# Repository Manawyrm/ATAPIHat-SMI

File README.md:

ATAPIHat-SMI
=============================

### Overview

This is an experimental adapter PCB for the pata-gpio driver.  
The pinout was chosen deliberately to support faster SMI and BCM2835 register modes,  
which are not yet supported in the kernel driver. 

Rev.A testboards were ordered but not tested yet. **Proceed at your own risk.** 

### Manufacturing

Manufacturing files for JLCs automatic assembly service can be found at `gerbers/RevA/ATAPIHat-SMI/`.  
5 adapter boards cost ~15$ (incl. components). 

### Additional info 

[Schematic](gerbers/RevA/ATAPIHat-SMI/ATAPIHat-SMI.pdf)  
[Interactive BOM](https://tbspace.de/content/downloads/atapihat-smi-ibom-reva.html)  
[Bitbanged-GPIO Kernel driver](https://github.com/Manawyrm/pata-gpio)  

### Credits
The PCB layout was done by [@Toble_Miner](https://github.com/TobleMiner)! Thanks!

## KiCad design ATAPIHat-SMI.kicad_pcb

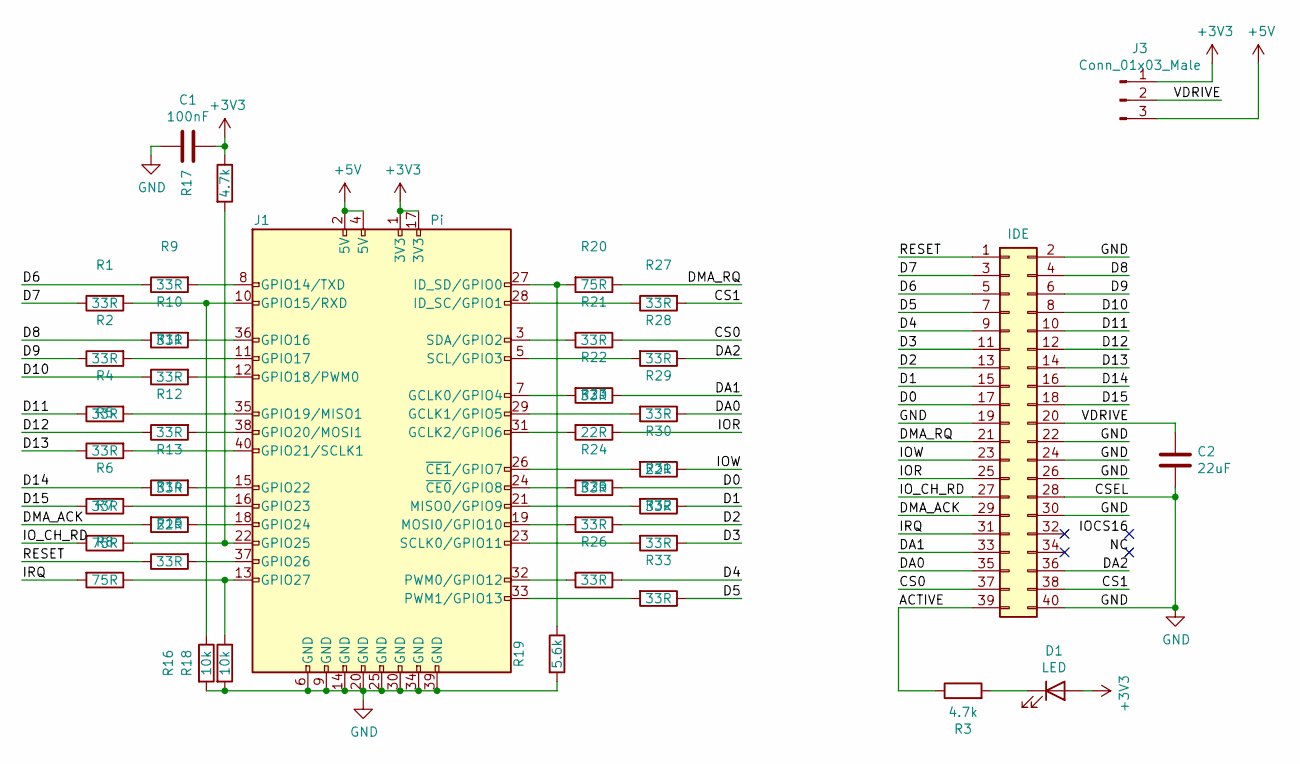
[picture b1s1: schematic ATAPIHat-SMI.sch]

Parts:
C1: 100nF; C_0402_1005Metric; LCSC C1525
C2: 22uF; C_0805_2012Metric; LCSC C45783
D1: LED; LED_0603_1608Metric; LCSC C72043
J1: Pi; PinSocket_2x20_P2.54mm_Vertical
J2: IDE; IDC-Header_2x20_P2.54mm_Vertical
J3: Conn_01x03_Male; SolderJumper-3_P1.3mm_Bridged12_Pad1.0x1.5mm
R1, R2, R4, R5, R6, R9, R10, R11, R12, R13, R15, R21, R22, R24, R25, R26, R27, R28, R29, R31, R32, R33: 33R; R_0402_1005Metric; LCSC C25105
R3, R17: 4.7k; R_0402_1005Metric; LCSC C25900
R7, R8, R20: 75R; R_0402_1005Metric; LCSC C25133
R14, R23, R30: 22R; R_0402_1005Metric; LCSC C25092
R16, R18: 10k; R_0402_1005Metric; LCSC C25744
R19: 5.6k; R_0402_1005Metric; LCSC C25908

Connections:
+3V3: C1.1, D1.2 (A), J1.1 (3V3), J1.17 (3V3), J3.1, R17.1
+5V: J1.2 (5V), J1.4 (5V), J3.3
/ACTIVE: J2.39, R3.1
/CS0: J2.37, R21.1
/CS1: J2.38, R27.2
/D0: J2.17, R24.1
/D1: J2.15, R31.1
/D2: J2.13, R25.1
/D3: J2.11, R32.1
/D4: J2.9, R26.1
/D5: J2.7, R33.1
/D6: J2.5, R9.1
/D7: J2.3, R1.1
/D8: J2.4, R10.1
/D9: J2.6, R2.1
/D10: J2.8, R11.1
/D11: J2.10, R4.1
/D12: J2.12, R12.1
/D13: J2.14, R5.1
/D14: J2.16, R13.1
/D15: J2.18, R6.1
/DA0: J2.35, R29.1
/DA1: J2.33, R22.1
/DA2: J2.36, R28.1
/DMA_ACK: J2.29, R14.2
/DMA_RQ: J2.21, R20.1
/IOR: J2.25, R23.1
/IOW: J2.23, R30.1
/IO_CH_RD: J2.27, R7.2
/IRQ: J2.31, R8.2
/RESET: J2.1, R15.1
/VDRIVE: C2.1, J2.20, J3.2
GND: C1.2, C2.2, J1.6 (GND), J1.9 (GND), J1.14 (GND), J1.20 (GND), J1.25 (GND), J1.30 (GND), J1.34 (GND), J1.39 (GND), J2.2, J2.19, J2.22, J2.24, J2.26, J2.28, J2.30, J2.40, R16.2, R18.2, R19.2
unnamed: D1.1 (K), R3.2
unnamed: J1.3 (SDA/GPIO2), R21.2
unnamed: J1.5 (SCL/GPIO3), R28.2
unnamed: J1.7 (GCLK0/GPIO4), R22.2
unnamed: J1.8 (GPIO14/TXD), R9.2
unnamed: J1.10 (GPIO15/RXD), R1.2, R16.1
unnamed: J1.11 (GPIO17), R2.2
unnamed: J1.12 (GPIO18/PWM0), R11.2
unnamed: J1.13 (GPIO27), R8.1, R18.1
unnamed: J1.15 (GPIO22), R13.2
unnamed: J1.16 (GPIO23), R6.2
unnamed: J1.18 (GPIO24), R14.1
unnamed: J1.19 (MOSI0/GPIO10), R25.2
unnamed: J1.21 (MISO0/GPIO9), R31.2
unnamed: J1.22 (GPIO25), R7.1, R17.2
unnamed: J1.23 (SCLK0/GPIO11), R32.2
unnamed: J1.24 (~CE0~/GPIO8), R24.2
unnamed: J1.26 (~CE1~/GPIO7), R30.2
unnamed: J1.27 (ID_SD/GPIO0), R19.1, R20.2
unnamed: J1.28 (ID_SC/GPIO1), R27.1
unnamed: J1.29 (GCLK1/GPIO5), R29.2
unnamed: J1.31 (GCLK2/GPIO6), R23.2
unnamed: J1.32 (PWM0/GPIO12), R26.2
unnamed: J1.33 (PWM1/GPIO13), R33.2
unnamed: J1.35 (GPIO19/MISO1), R4.2
unnamed: J1.36 (GPIO16), R10.2
unnamed: J1.37 (GPIO26), R15.2
unnamed: J1.38 (GPIO20/MOSI1), R12.2
unnamed: J1.40 (GPIO21/SCLK1), R5.2

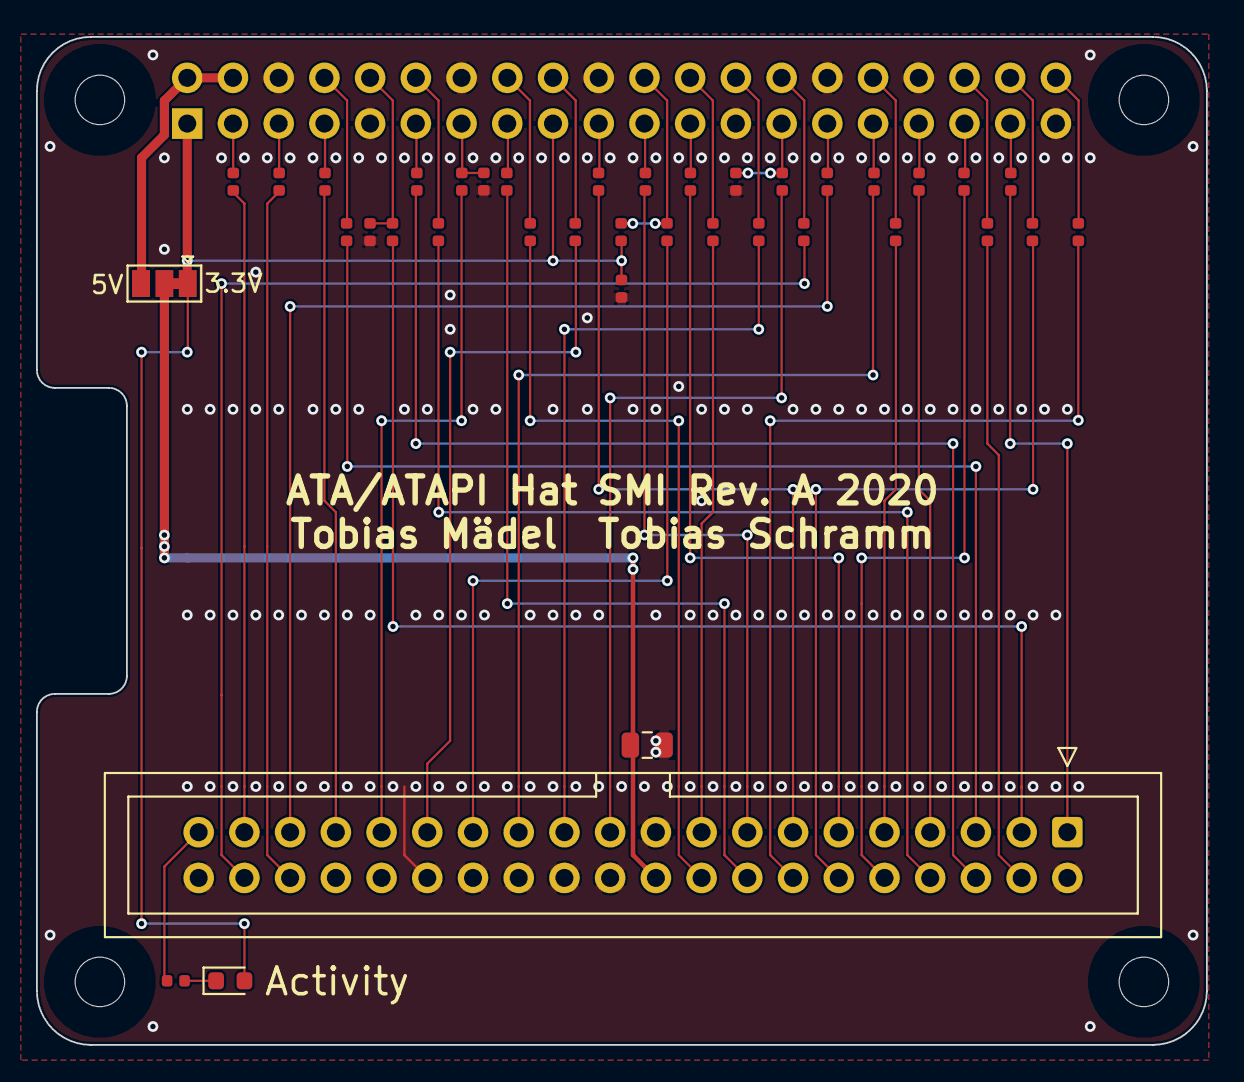
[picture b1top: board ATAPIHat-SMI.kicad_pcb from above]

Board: 2 copper layers, 65.0 x 56.0 mm, 39 parts (1 on the bottom side), 62 nets.

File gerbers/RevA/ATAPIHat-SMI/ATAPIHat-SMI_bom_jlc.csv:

"Comment","Designator","Footprint","LCSC Part #"
"100nF","C1","C_0402_1005Metric","C1525"
"22uF","C2","C_0805_2012Metric","C45783"
"LED","D1","LED_0603_1608Metric","C72043"
"4.7k","R3,R17","R_0402_1005Metric","C25900"
"75R","R8,R7,R20","R_0402_1005Metric","C25133"
"10k","R16,R18","R_0402_1005Metric","C25744"
"5.6k","R19","R_0402_1005Metric","C25908"
"22R","R23,R30,R14","R_0402_1005Metric","C25092"
"33R","R24,R31,R25,R32,R26,R33,R9,R1,R2,R10,R11,R4,R12,R5,R13,R6,R29,R22,R28,R21,R15,R27","R_0402_1005Metric","C25105"

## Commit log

2020-08-08 Add initial schematic
2020-08-09 Correct cable select
2020-08-09 Do layout
2020-08-09 Center hat name
2020-08-12 Add gerber, manufacturing files and README
2020-08-16 Add tooling holes
